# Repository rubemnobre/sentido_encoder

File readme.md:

sentido_encoder
============

Digital circuit to indicate the direction of spin of a quadrature pulse encoder.

###  Motivation

This circuit was developed to reduce the need for specific quadrature pulse encoder peripherals on the Controller Board of a robotics system with a large amount of encoders. It is designed to go inline with the encoder cable, read one of the pulse channels and pass it forward, and use it's relation with the other one to drive an open collector output indicating the direction of spin.

### Architecture

The usage of a small and low cost microcontroller allows for a very simple circuit, with only a LDO to supply the 5V rail, optional pull down resistors on the A and B lines to provide adaptability for different encoder output types, and a BJT with an open collector output for the direction signal.

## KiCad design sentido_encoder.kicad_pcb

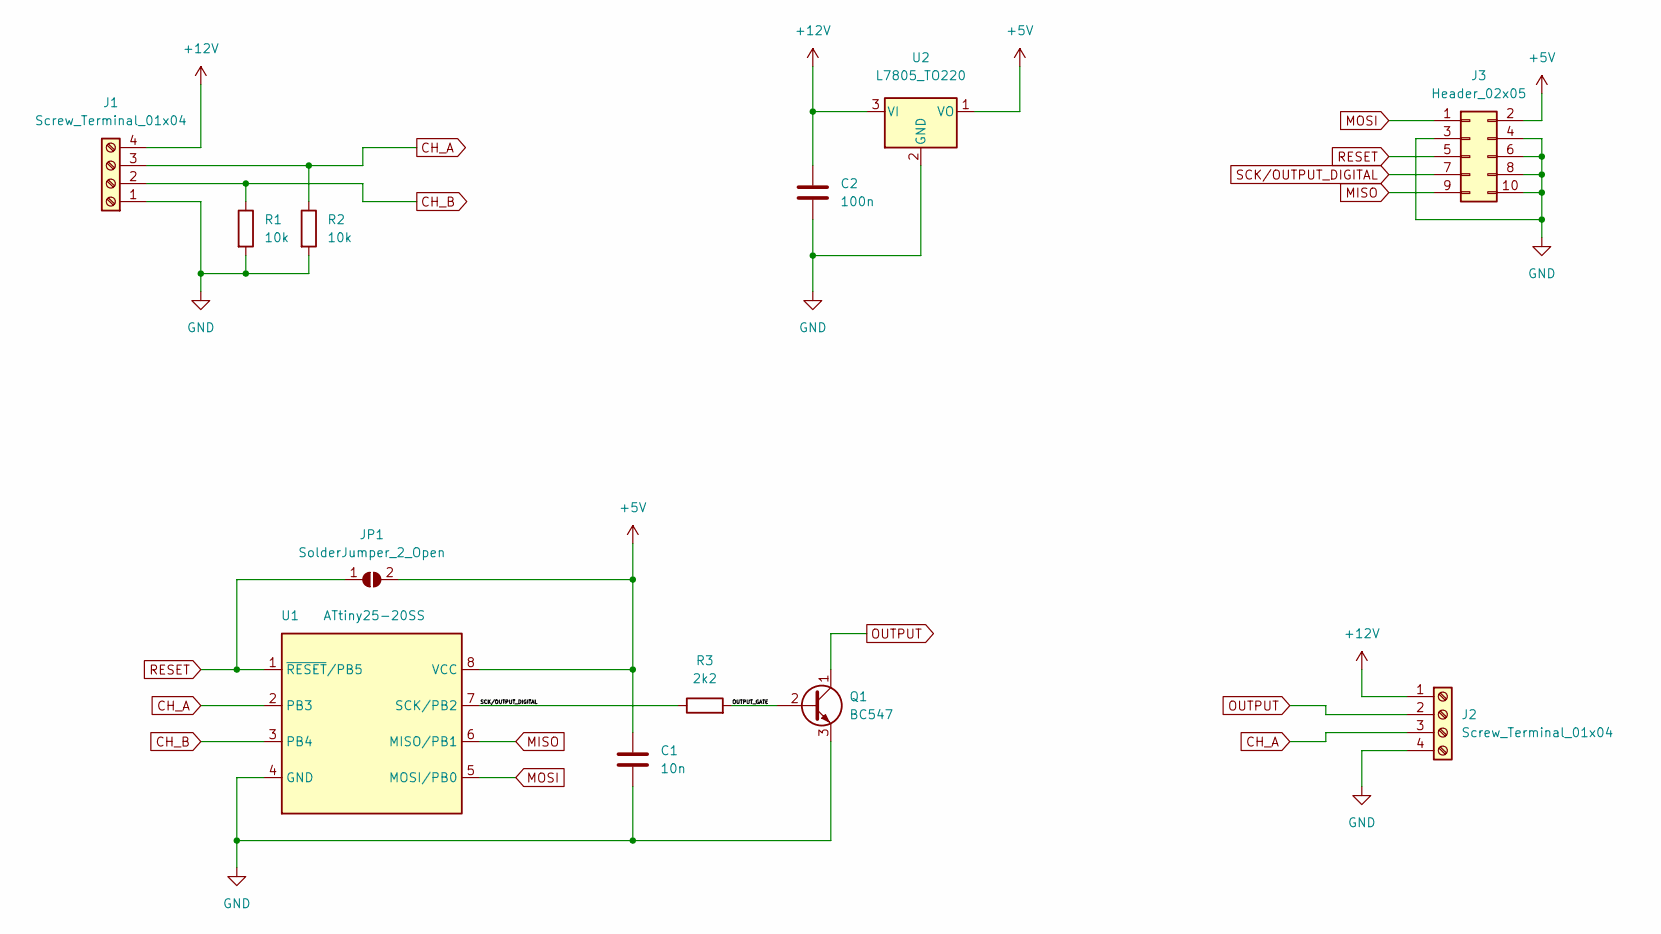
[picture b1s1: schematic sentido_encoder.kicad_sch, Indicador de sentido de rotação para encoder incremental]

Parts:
C1: 10n; C_Disc_D5.0mm_W2.5mm_P5.00mm
C2: 100n; C_Disc_D5.0mm_W2.5mm_P5.00mm
J1, J2: Screw_Terminal_01x04; TerminalBlock_RND_205-00234_1x04_P5.08mm_Horizontal
J3: Header_02x05; PinHeader_2x05_P2.54mm_Vertical
JP1: SolderJumper_2_Open; R_0805_2012Metric_Pad1.20x1.40mm_HandSolder
Q1: BC547; TO-92_Inline_Wide
R1, R2: 10k; R_Axial_DIN0207_L6.3mm_D2.5mm_P10.16mm_Horizontal
R3: 2k2; R_Axial_DIN0207_L6.3mm_D2.5mm_P10.16mm_Horizontal
U1: ATtiny25-20SS; SOIC-8_3.9x4.9mm_P1.27mm
U2: L7805_TO220; TO-220-3_Horizontal_TabDown

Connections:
+5V: C1.1, J3.2, JP1.2 (B), U1.8 (VCC), U2.1 (VO)
+12V: C2.1, J1.4, J2.1, U2.3 (VI)
/OUTPUT_GATE: Q1.2 (B), R3.2
CH_A: J1.3, J2.3, R2.1, U1.2 (PB3)
CH_B: J1.2, R1.1, U1.3 (PB4)
GND: C1.2, C2.2, J1.1, J2.4, J3.3, J3.4, J3.6, J3.8, J3.10, Q1.3 (E), R1.2, R2.2, U1.4 (GND), U2.2 (GND)
MISO: J3.9, U1.6 (MISO/PB1)
MOSI: J3.1, U1.5 (MOSI/PB0)
OUTPUT: J2.2, Q1.1 (C)
RESET: J3.5, JP1.1 (A), U1.1 (~RESET/PB5)
SCK/OUTPUT_DIGITAL: J3.7, R3.1, U1.7 (SCK/PB2)

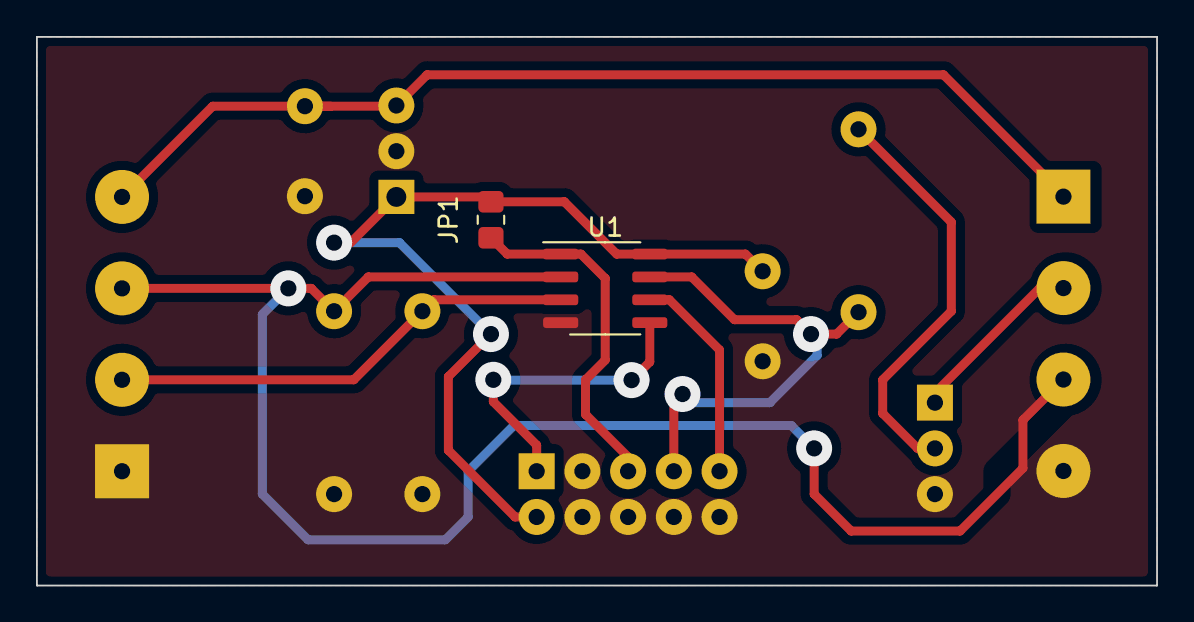
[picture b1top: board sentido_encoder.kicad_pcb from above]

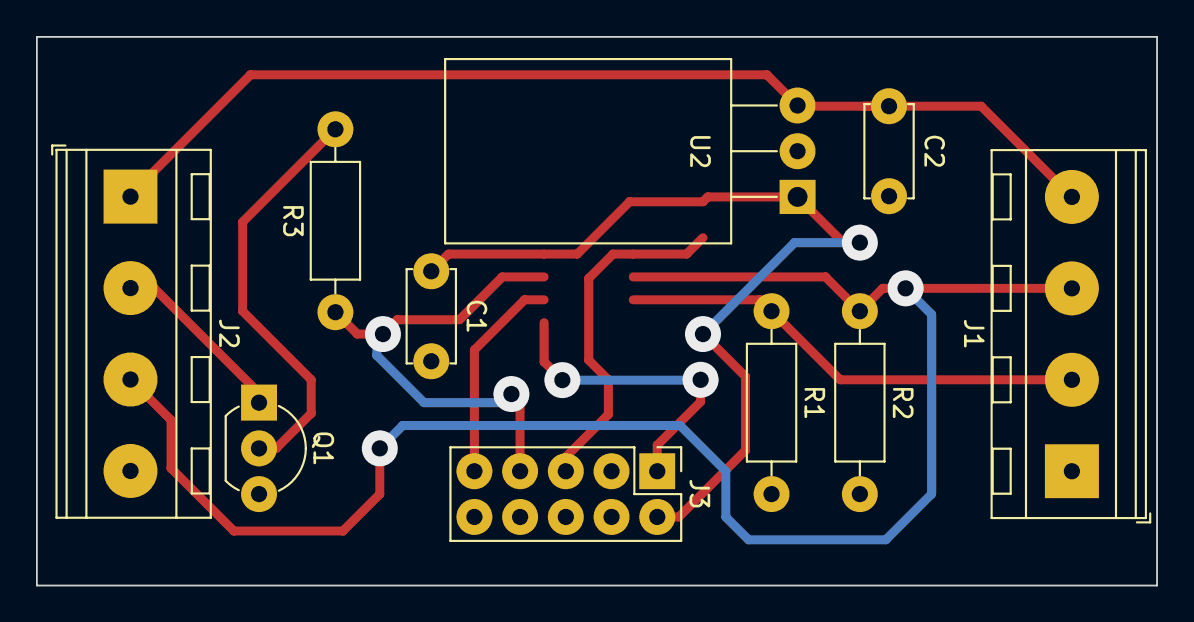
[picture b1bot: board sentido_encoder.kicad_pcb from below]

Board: 2 copper layers, 62.2 x 30.5 mm, 12 parts (10 on the bottom side), 11 nets.

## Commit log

2023-02-28 add readme
